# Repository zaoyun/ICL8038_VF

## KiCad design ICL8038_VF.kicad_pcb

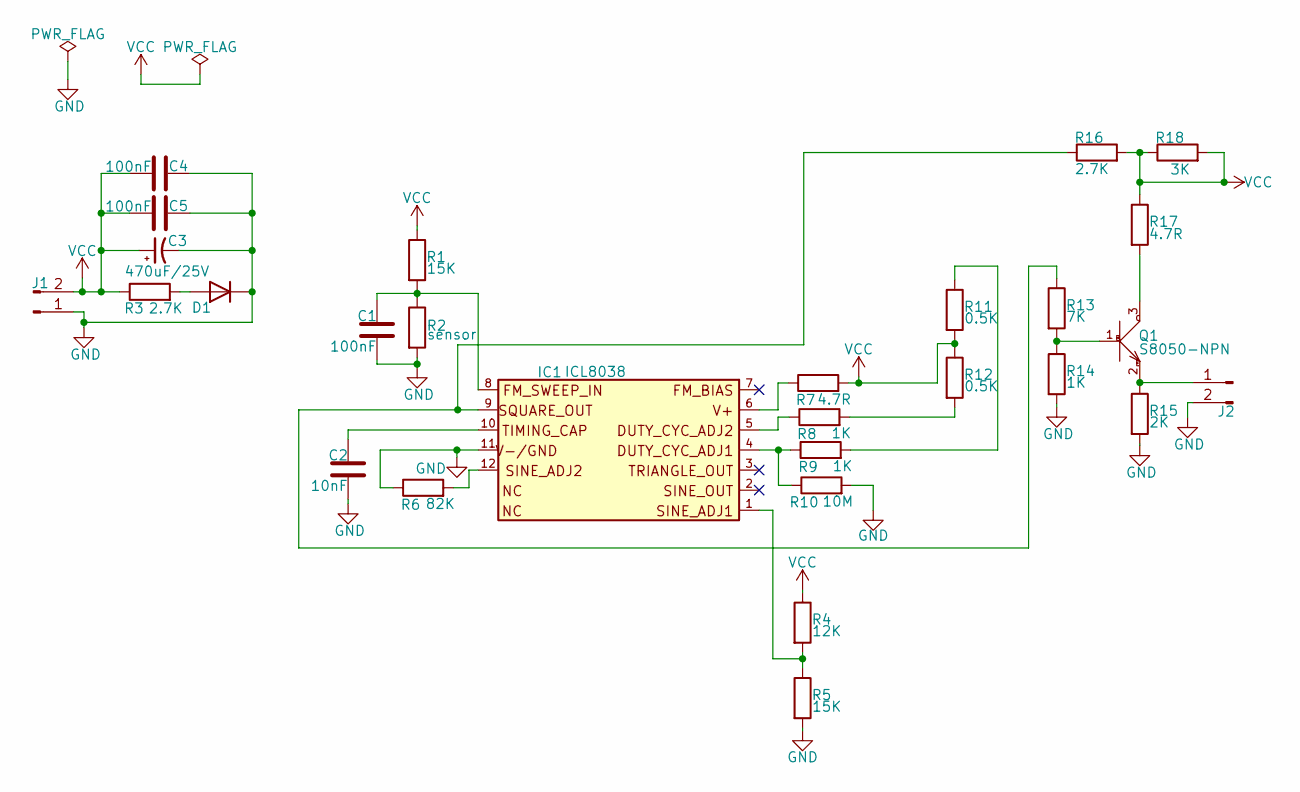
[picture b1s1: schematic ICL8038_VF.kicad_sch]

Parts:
C1, C4, C5: 100nF; C_0603_1608Metric
C2: 10nF; C_0603_1608Metric
C3: 470uF/25V; CP_Radial_D8.0mm_P3.50mm
D1: type="D" model="red" lib=""; D_0603_1608Metric
IC1: ICL8038; PDIP14_7P11X19P68_INR
J1: Conn_01x02_Male; AMASS_XT30U-F_1x02_P5.0mm_Vertical
J2: Conn_01x02_Male; PinSocket_1x02_P2.54mm_Vertical
Q1: S8050-NPN; SOT-23; MPN S8050
R1, R5: 15K; R_0603_1608Metric
R2: sensor; PinSocket_1x02_P2.54mm_Vertical
R3, R16: 2.7K; R_0603_1608Metric
R4: 12K; R_0603_1608Metric
R6: 82K; R_0603_1608Metric
R7, R17: 4.7R; R_0603_1608Metric
R8, R9, R14: 1K; R_0603_1608Metric
R10: 10M; R_0603_1608Metric
R11, R12: 0.5K; R_0603_1608Metric
R13: 7K; R_0603_1608Metric
R15: 2K; R_0603_1608Metric
R18: 3K; R_0603_1608Metric

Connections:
GND: C1.2, C2.2, C3.2, C4.1, C5.1, D1.2 (K), IC1.11, J1.1, J2.2, R2.2, R5.2, R6.1, R10.2, R14.2, R15.2
unnamed: C1.1, IC1.8, R1.2, R2.1
unnamed: C2.1, IC1.10
unnamed: D1.1 (A), R3.2
unnamed: IC1.1, R4.2, R5.1
unnamed: IC1.4, R9.1, R10.1
unnamed: IC1.5, R8.1
unnamed: IC1.6, R7.1
unnamed: IC1.9, R13.1, R16.1
unnamed: IC1.12, R6.2
unnamed: J2.1, Q1.2, R15.1
unnamed: Q1.1, R13.2, R14.1
unnamed: Q1.3, R17.2
unnamed: R9.2, R11.1
unnamed: R8.2, R12.2
VCC: C3.1, C4.2, C5.2, J1.2, R1.1, R3.1, R4.1, R7.2, R11.2, R12.1, R16.2, R17.1, R18.1, R18.2

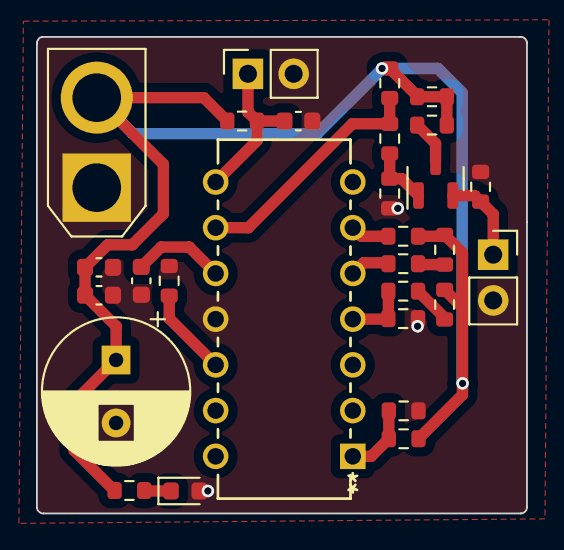
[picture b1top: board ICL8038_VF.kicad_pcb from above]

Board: 2 copper layers, 27.2 x 26.5 mm, 28 parts (0 on the bottom side), 16 nets.
